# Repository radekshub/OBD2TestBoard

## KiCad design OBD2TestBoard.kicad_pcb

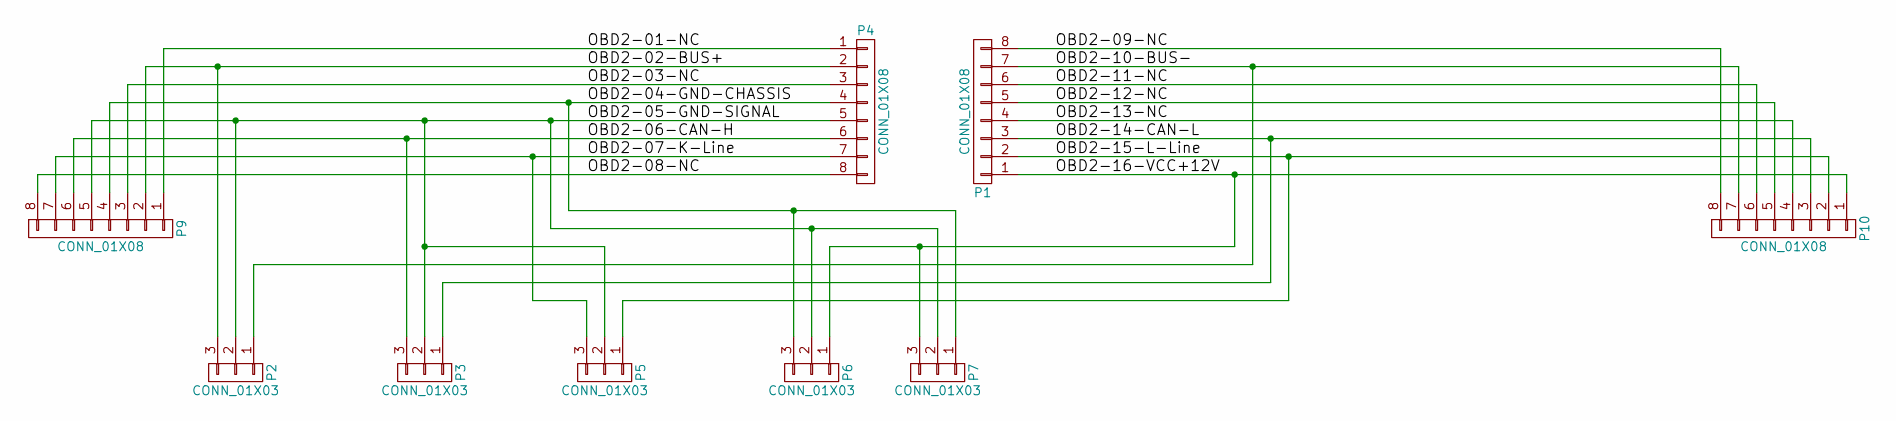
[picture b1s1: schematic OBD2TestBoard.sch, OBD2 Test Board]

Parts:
P1, P4, P9, P10: CONN_01X08; Pin_Header_Straight_1x08
P2, P3, P5, P6, P7: CONN_01X03; AK300-3

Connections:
/OBD2-01-NC: P4.1, P9.1
/OBD2-02-BUS+: P2.3, P4.2, P9.2
/OBD2-03-NC: P4.3, P9.3
/OBD2-04-GND-CHASSIS: P4.4, P6.3, P7.1, P9.4
/OBD2-05-GND-SIGNAL: P2.2, P3.2, P4.5, P5.2, P6.2, P7.2, P9.5
/OBD2-06-CAN-H: P3.3, P4.6, P9.6
/OBD2-07-K-Line: P4.7, P5.3, P9.7
/OBD2-08-NC: P4.8, P9.8
/OBD2-09-NC: P1.8, P10.8
/OBD2-10-BUS-: P1.7, P2.1, P10.7
/OBD2-11-NC: P1.6, P10.6
/OBD2-12-NC: P1.5, P10.5
/OBD2-13-NC: P1.4, P10.4
/OBD2-14-CAN-L: P1.3, P3.1, P10.3
/OBD2-15-L-Line: P1.2, P5.1, P10.2
/OBD2-16-VCC+12V: P1.1, P6.1, P7.3, P10.1

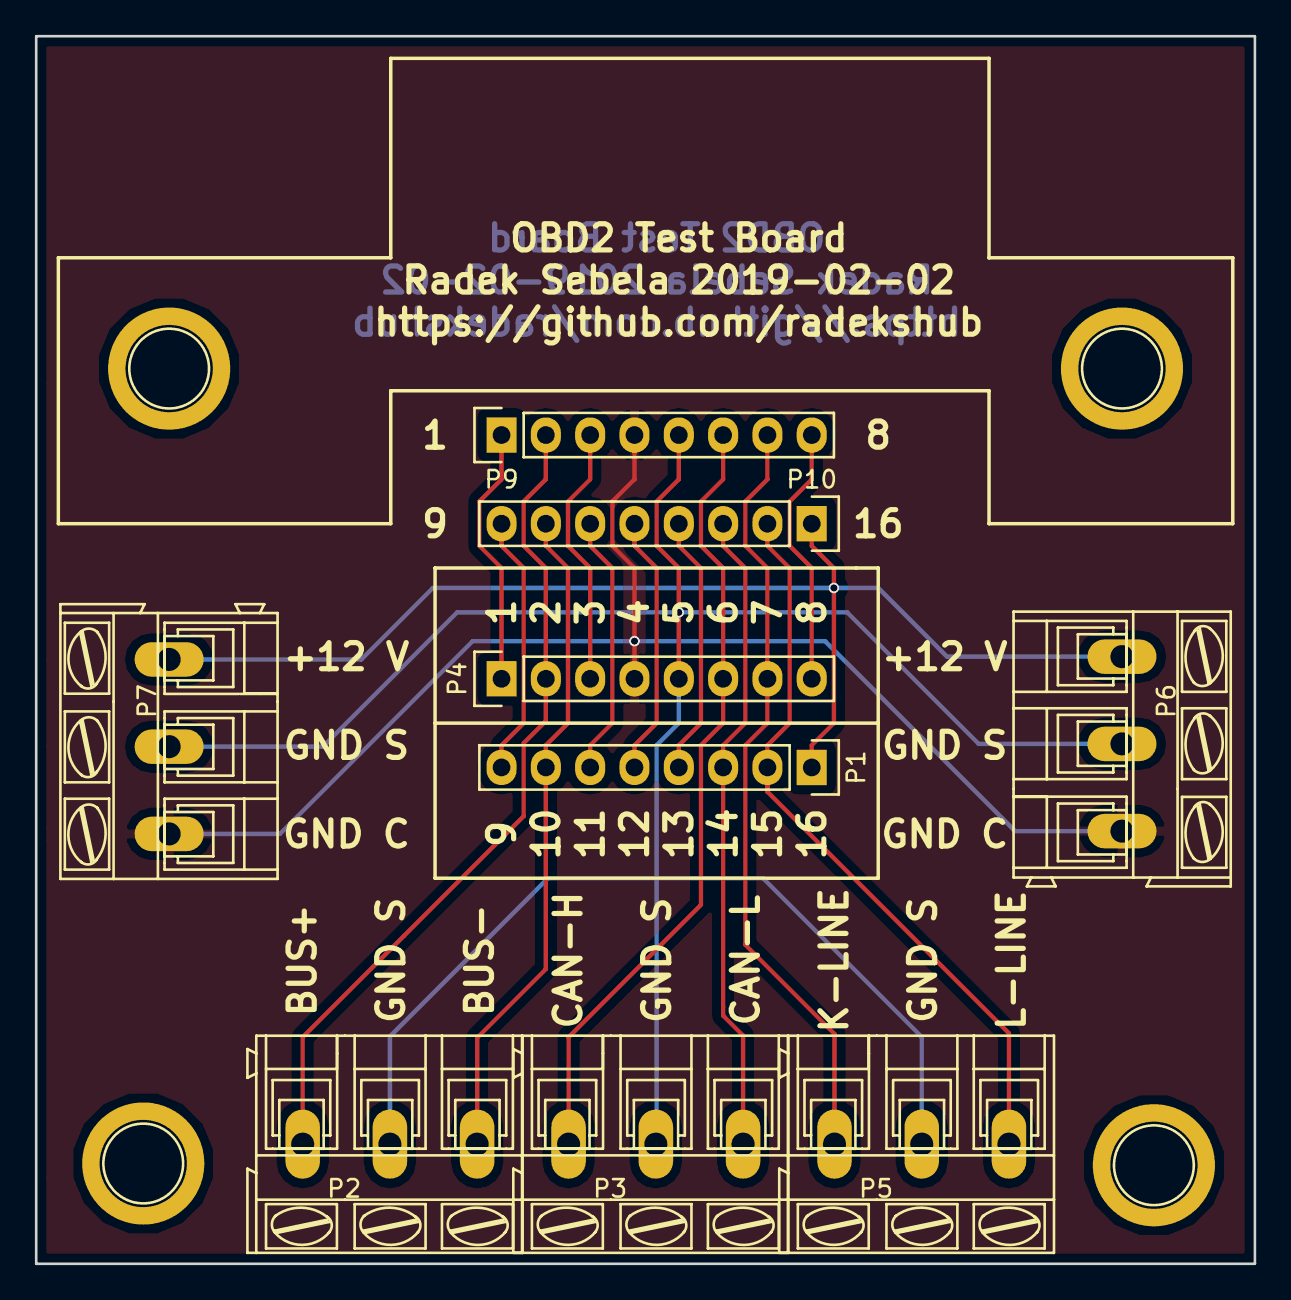
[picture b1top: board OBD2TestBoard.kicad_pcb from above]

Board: 2 copper layers, 69.9 x 70.4 mm, 9 parts (0 on the bottom side), 16 nets.

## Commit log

2019-02-10 Add files via upload
    Add files revision 1.1
